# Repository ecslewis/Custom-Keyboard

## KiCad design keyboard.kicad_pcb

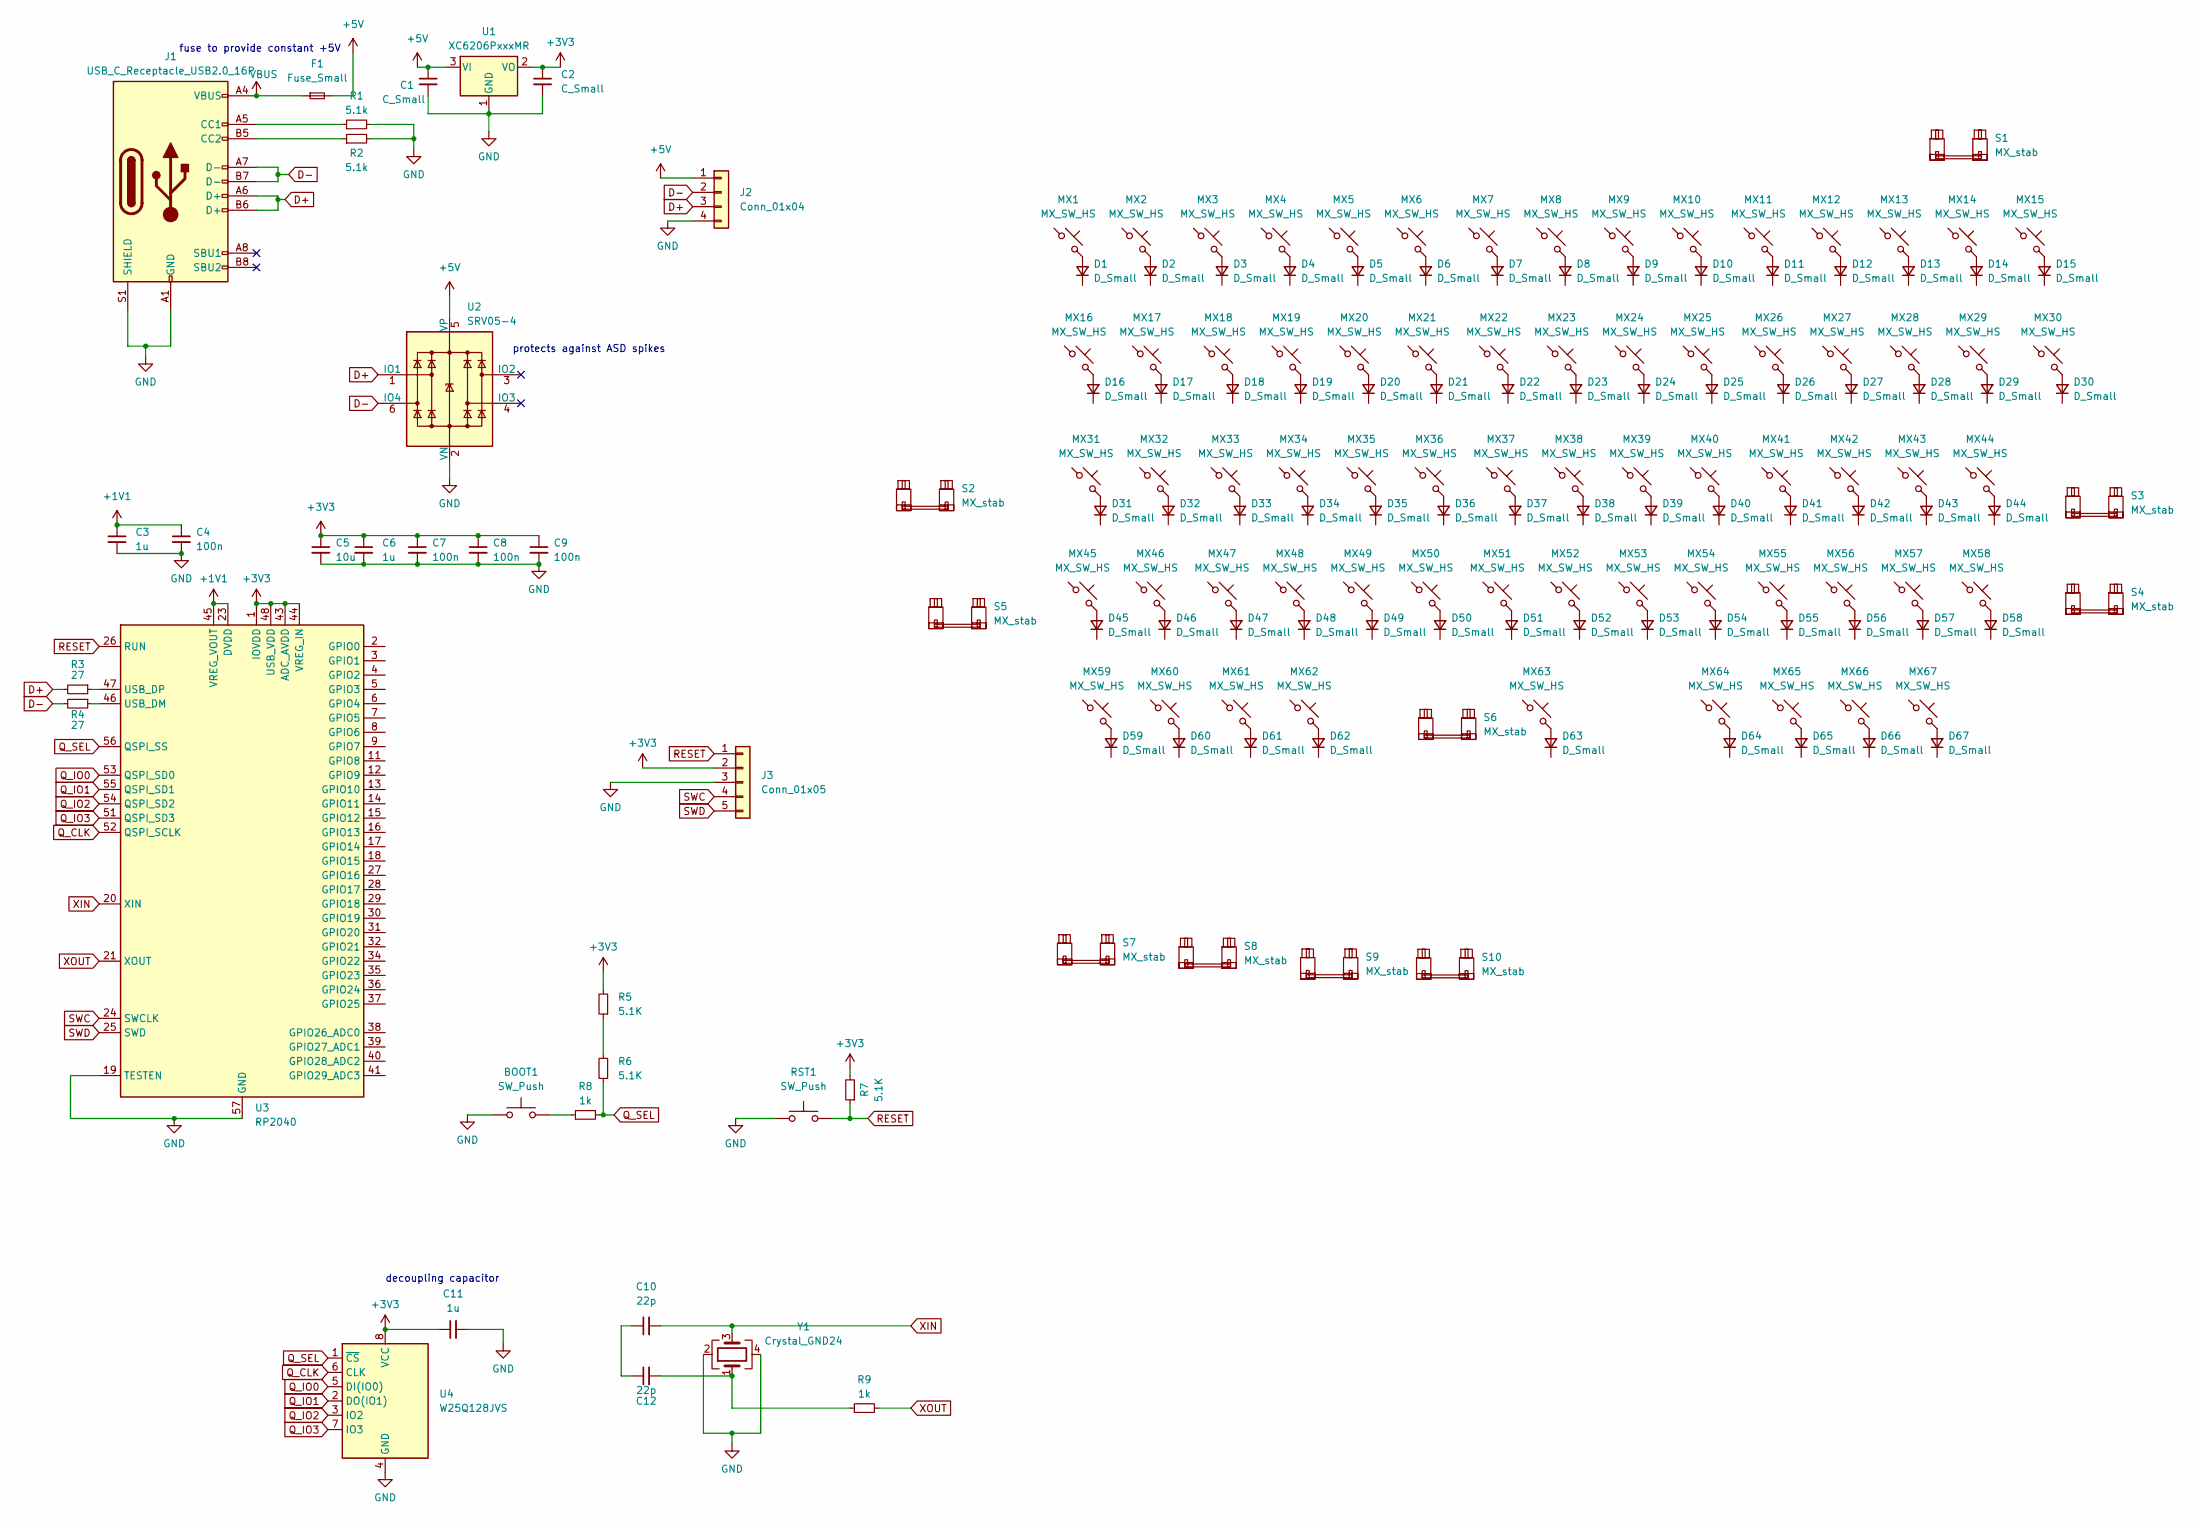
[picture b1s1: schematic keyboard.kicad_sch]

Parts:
BOOT1: SW_Push; SW_SPST_TL3342
C1, C2: C_Small; C_0402_1005Metric
C3, C6, C11: 1u; C_0402_1005Metric
C4, C7, C8, C9: 100n; C_0402_1005Metric
C5: 10u; C_0603_1608Metric
C10, C12: 22p; C_0402_1005Metric
D1, D2, D3, D4, D5, D6, D7, D8, D9, D10, D11, D12, D13, D14, D15, D16, D17, D18, D19, D20, D21, D22, D23, D24, D25, D26, D27, D28, D29, D30, D31, D32, D33, D34, D35, D36, D37, D38, D39, D40, D41, D42, D43, D44, D45, D46, D47, D48, D49, D50, D51, D52, D53, D54, D55, D56, D57, D58, D59, D60, D61, D62, D63, D64, D65, D66, D67: D_Small; D_SOD-123
F1: Fuse_Small; Fuse_1206_3216Metric
J1: USB_C_Receptacle_USB2.0_16P; USB_C_Receptacle_HRO_TYPE-C-31-M-12
J2: Conn_01x04; JST_SH_SM04B-SRSS-TB_1x04-1MP_P1.00mm_Horizontal
J3: Conn_01x05; PinHeader_1x05_P2.54mm_Vertical
MX1, MX2, MX3, MX4, MX5, MX6, MX7, MX8, MX9, MX10, MX11, MX12, MX13, MX15, MX17, MX18, MX19, MX20, MX21, MX22, MX23, MX24, MX25, MX26, MX27, MX28, MX29, MX30, MX32, MX33, MX34, MX35, MX36, MX37, MX38, MX39, MX40, MX41, MX42, MX44, MX46, MX47, MX48, MX49, MX50, MX51, MX52, MX53, MX54, MX55, MX57, MX58, MX59, MX60, MX61, MX63, MX65, MX66, MX67: MX_SW_HS; SW_MX_1u
MX14, MX31, MX43, MX56: MX_SW_HS; SW_MX_1.5u
MX16, MX62, MX64: MX_SW_HS; SW_MX_1.25u
MX45: MX_SW_HS; SW_MX_1.75u
R1, R2: 5.1k; R_01005_0402Metric
R3, R4: 27; R_01005_0402Metric
R5, R6, R7: 5.1K; R_01005_0402Metric
R8, R9: 1k; R_01005_0402Metric
RST1: SW_Push; SW_SPST_TL3342
S1: MX_stab; STAB_MX_P_1.5u
S2, S3: MX_stab; STAB_MX_P_1.75u
S4, S5, S7, S8, S9, S10: MX_stab; STAB_MX_P_2u
S6: MX_stab; STAB_MX_P_6.25u
U1: XC6206PxxxMR; SOT-23-3
U2: SRV05-4; SOT-23-6-routable
U3: RP2040; QFN-56-1EP_7x7mm_P0.4mm_EP3.2x3.2mm
U4: W25Q128JVS; SOIC-8_5.23x5.23mm_P1.27mm
Y1: Crystal_GND24; Crystal_SMD_3225-4Pin_3.2x2.5mm

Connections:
+1V1: C3.1, C4.1, U3.23 (DVDD), U3.45 (VREG_VOUT), U3.50 (DVDD)
+3V3: C2.1, C5.1, C6.1, C7.1, C8.1, C9.1, C11.1, J3.2, R5.2, R7.2, U1.2 (VO), U3.1 (IOVDD), U3.10 (IOVDD), U3.22 (IOVDD), U3.33 (IOVDD), U3.42 (IOVDD), U3.43 (ADC_AVDD), U3.44 (VREG_IN), U3.48 (USB_VDD), U3.49 (IOVDD), U4.8 (VCC)
+5V: C1.1, F1.2, J2.1, U1.3 (VI), U2.5 (VP)
D+: J1.A6 (D+), J1.B6 (D+), J2.3, R3.2, U2.1 (IO1)
D-: J1.A7 (D-), J1.B7 (D-), J2.2, R4.2, U2.6 (IO4)
GND: BOOT1.1, C1.2, C2.2, C3.2, C4.2, C5.2, C6.2, C7.2, C8.2, C9.2, C11.2, J1.A1 (GND), J1.A12 (GND), J1.B1 (GND), J1.B12 (GND), J1.S1 (SHIELD), J2.4, J3.3, R1.2, R2.2, RST1.1, U1.1 (GND), U2.2 (VN), U3.19 (TESTEN), U3.57 (GND), U4.4 (GND), Y1.2, Y1.4
unnamed: BOOT1.2, R8.1
unnamed: C10.1, C12.1
unnamed: C12.2, R9.1, Y1.1
unnamed: D1.2 (A), MX1.2
unnamed: D2.2 (A), MX2.2
unnamed: D3.2 (A), MX3.2
unnamed: D4.2 (A), MX4.2
unnamed: D5.2 (A), MX5.2
unnamed: D6.2 (A), MX6.2
unnamed: D7.2 (A), MX7.2
unnamed: D8.2 (A), MX8.2
unnamed: D9.2 (A), MX9.2
unnamed: D10.2 (A), MX10.2
unnamed: D11.2 (A), MX11.2
unnamed: D12.2 (A), MX12.2
unnamed: D13.2 (A), MX13.2
unnamed: D14.2 (A), MX14.2
unnamed: D15.2 (A), MX15.2
unnamed: D16.2 (A), MX16.2
unnamed: D17.2 (A), MX17.2
unnamed: D18.2 (A), MX18.2
unnamed: D19.2 (A), MX19.2
unnamed: D20.2 (A), MX20.2
unnamed: D21.2 (A), MX21.2
unnamed: D22.2 (A), MX22.2
unnamed: D23.2 (A), MX23.2
unnamed: D24.2 (A), MX24.2
unnamed: D25.2 (A), MX25.2
unnamed: D26.2 (A), MX26.2
unnamed: D27.2 (A), MX27.2
unnamed: D28.2 (A), MX28.2
unnamed: D29.2 (A), MX29.2
unnamed: D30.2 (A), MX30.2
unnamed: D31.2 (A), MX31.2
unnamed: D32.2 (A), MX32.2
unnamed: D33.2 (A), MX33.2
unnamed: D34.2 (A), MX34.2
unnamed: D35.2 (A), MX35.2
unnamed: D36.2 (A), MX36.2
unnamed: D37.2 (A), MX37.2
unnamed: D38.2 (A), MX38.2
unnamed: D39.2 (A), MX39.2
unnamed: D40.2 (A), MX40.2
unnamed: D41.2 (A), MX41.2
unnamed: D42.2 (A), MX42.2
unnamed: D43.2 (A), MX43.2
unnamed: D44.2 (A), MX44.2
unnamed: D45.2 (A), MX45.2
unnamed: D46.2 (A), MX46.2
unnamed: D47.2 (A), MX47.2
unnamed: D48.2 (A), MX48.2
unnamed: D49.2 (A), MX49.2
unnamed: D50.2 (A), MX50.2
unnamed: D51.2 (A), MX51.2
unnamed: D52.2 (A), MX52.2
unnamed: D53.2 (A), MX53.2
unnamed: D54.2 (A), MX54.2
unnamed: D55.2 (A), MX55.2
unnamed: D56.2 (A), MX56.2
unnamed: D57.2 (A), MX57.2
unnamed: D58.2 (A), MX58.2
unnamed: D59.2 (A), MX59.2
unnamed: D60.2 (A), MX60.2
unnamed: D61.2 (A), MX61.2
unnamed: D62.2 (A), MX62.2
unnamed: D63.2 (A), MX63.2
unnamed: D64.2 (A), MX64.2
unnamed: D65.2 (A), MX65.2
unnamed: D66.2 (A), MX66.2
unnamed: D67.2 (A), MX67.2
unnamed: J1.A5 (CC1), R1.1
unnamed: J1.B5 (CC2), R2.1
unnamed: R5.1, R6.2
unnamed: R4.1, U3.46 (USB_DM)
unnamed: R3.1, U3.47 (USB_DP)
Q_CLK: U3.52 (QSPI_SCLK), U4.6 (CLK)
Q_IO0: U3.53 (QSPI_SD0), U4.5 (DI(IO0))
Q_IO1: U3.55 (QSPI_SD1), U4.2 (DO(IO1))
Q_IO2: U3.54 (QSPI_SD2), U4.3 (IO2)
Q_IO3: U3.51 (QSPI_SD3), U4.7 (IO3)
Q_SEL: R6.1, R8.2, U3.56 (QSPI_SS), U4.1 (~CS)
RESET: J3.1, R7.1, RST1.2, U3.26 (RUN)
SWC: J3.4, U3.24 (SWCLK)
SWD: J3.5, U3.25 (SWD)
VBUS: F1.1, J1.A4 (VBUS), J1.A9 (VBUS), J1.B4 (VBUS), J1.B9 (VBUS)
XIN: C10.2, U3.20 (XIN), Y1.3
XOUT: R9.2, U3.21 (XOUT)

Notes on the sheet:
fuse to provide constant +5V
protects against ASD spikes
decoupling capacitor

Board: 2 copper layers, 169 parts (0 on the bottom side), 93 nets, no tracks yet.

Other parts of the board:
S4#2: MX_stab; STAB_MX_P_2u

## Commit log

2025-05-20 changes to schematics
